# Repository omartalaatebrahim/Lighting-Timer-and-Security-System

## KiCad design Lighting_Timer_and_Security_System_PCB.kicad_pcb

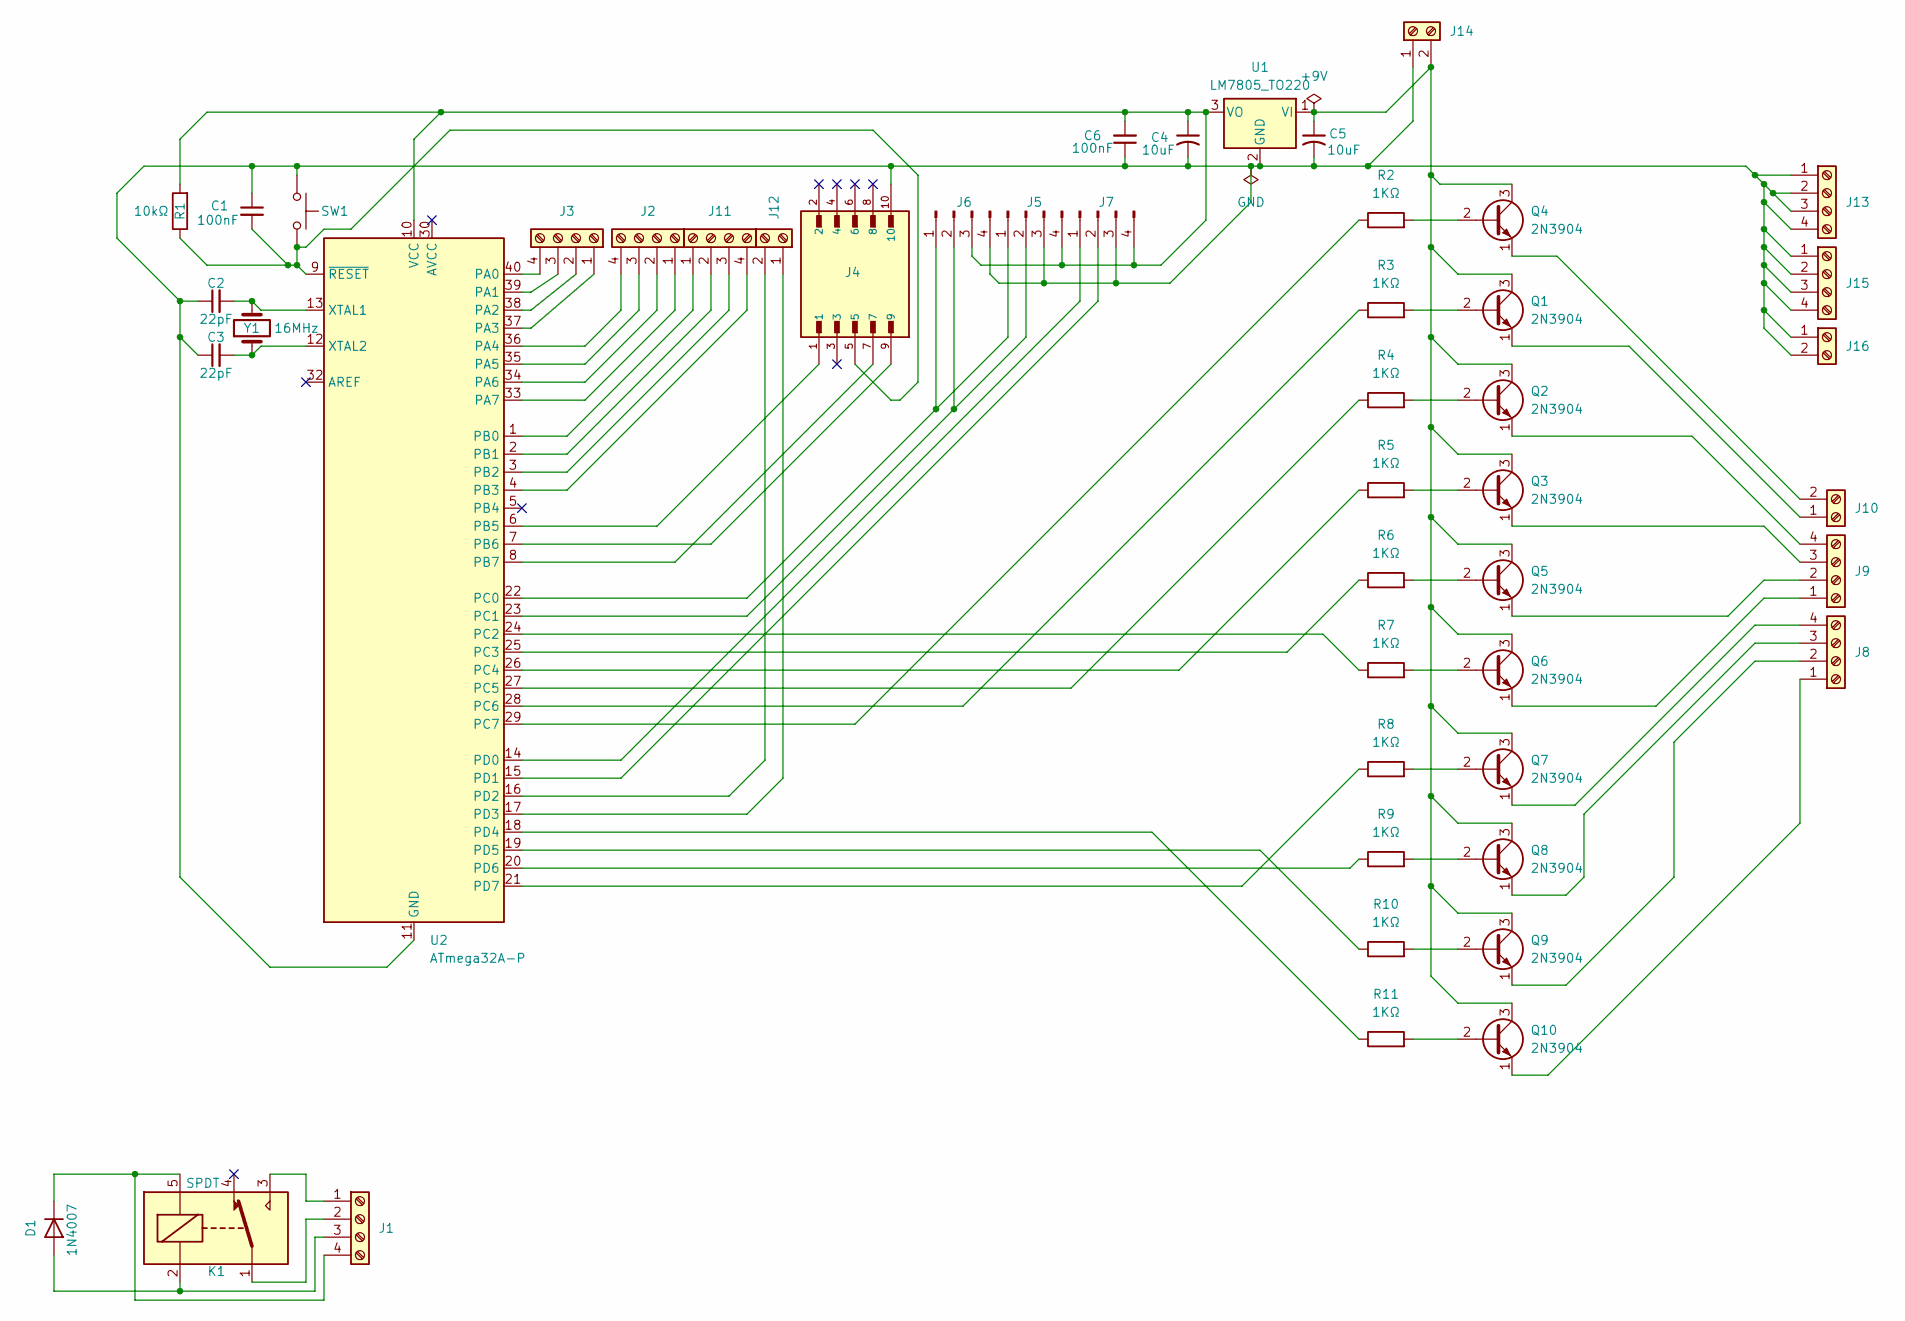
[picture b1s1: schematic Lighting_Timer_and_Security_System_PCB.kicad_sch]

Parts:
C1, C6: 100nF; C_Disc_D5.0mm_W2.5mm_P5.00mm
C2, C3: 22pF; C_Disc_D5.0mm_W2.5mm_P5.00mm
C4, C5: 10uF; CP_Radial_D5.0mm_P2.50mm
D1: 1N4007; D_DO-41_SOD81_P10.16mm_Horizontal
J1: T; TerminalBlock_MaiXu_MX126-5.0-04P_1x04_P5.00mm
J2, J3, J11: A0_A3_Terminals; TerminalBlock_MaiXu_MX126-5.0-04P_1x04_P5.00mm
J4: SBH11-PBPC-D05-ST-BK; SULLINS_SBH11-PBPC-D05-ST-BK; PARTREV J
J5: I2C; PinHeader_1x04_P2.54mm_Vertical
J6: DS3231_Timer; PinHeader_1x04_P2.54mm_Vertical
J7: UART; PinHeader_1x04_P2.54mm_Vertical
J8, J9: SIG_Terminals; TerminalBlock_MaiXu_MX126-5.0-04P_1x04_P5.00mm
J10: SIG_Terminals; TerminalBlock_MaiXu_MX126-5.0-02P_1x02_P5.00mm
J12, J14: Screw_Terminal_01x02; TerminalBlock_MaiXu_MX126-5.0-02P_1x02_P5.00mm
J13, J15: GND_Terminals; TerminalBlock_MaiXu_MX126-5.0-04P_1x04_P5.00mm
J16: GND_Terminals; TerminalBlock_MaiXu_MX126-5.0-02P_1x02_P5.00mm
K1: SPDT; Relay_SPDT_SANYOU_SRD_Series_Form_C
Q1, Q2, Q3, Q4, Q5, Q6, Q7, Q8, Q9, Q10: 2N3904; TO-92_Inline
R1: 10kΩ; R_Axial_DIN0207_L6.3mm_D2.5mm_P7.62mm_Horizontal
R2, R3, R4, R5, R6, R7, R8, R9, R10, R11: 1KΩ; R_Axial_DIN0207_L6.3mm_D2.5mm_P7.62mm_Horizontal
SW1: SW_Push; SW_PUSH_6mm
U1: LM7805_TO220; TO-220-3_Vertical
U2: ATmega32A-P; DIP-40_W15.24mm
Y1: 16MHz; Crystal_HC49-U_Vertical

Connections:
unnamed: D1.2 (A), J1.3, K1.2
unnamed: D1.1 (K), J1.4, K1.5
unnamed: J1.1, K1.3
unnamed: J1.2, K1.1
unnamed: J2.1, U2.33 (PA7)
unnamed: J2.2, U2.34 (PA6)
unnamed: J2.3, U2.35 (PA5)
unnamed: J2.4, U2.36 (PA4)
unnamed: J3.1, U2.37 (PA3)
unnamed: J3.2, U2.38 (PA2)
unnamed: J3.3, U2.39 (PA1)
unnamed: J3.4, U2.40 (PA0)
unnamed: J5.1, J6.1, U2.22 (PC0)
unnamed: J5.2, J6.2, U2.23 (PC1)
unnamed: C4.1, C6.2, J5.4, J6.3, J7.4, R1.2, U1.3 (VO), U2.10 (VCC)
unnamed: J7.1, U2.14 (PD0)
unnamed: J7.2, U2.15 (PD1)
unnamed: J8.1, Q10.1 (E)
unnamed: J8.2, Q9.1 (E)
unnamed: J8.3, Q8.1 (E)
unnamed: J8.4, Q7.1 (E)
unnamed: J9.1, Q6.1 (E)
unnamed: J9.2, Q5.1 (E)
unnamed: J9.3, Q3.1 (E)
unnamed: J9.4, Q2.1 (E)
unnamed: J10.1, Q1.1 (E)
unnamed: J10.2, Q4.1 (E)
unnamed: J11.1, U2.1 (PB0)
unnamed: J11.2, U2.2 (PB1)
unnamed: J11.3, U2.3 (PB2)
unnamed: J11.4, U2.4 (PB3)
unnamed: J12.1, U2.17 (PD3)
unnamed: J12.2, U2.16 (PD2)
unnamed: C1.1, C2.1, C3.1, C4.2, C5.2, C6.1, J4.10, J5.3, J6.4, J7.3, J13.1, J13.2, J13.3, J13.4, J14.1, J15.1, J15.2, J15.3, J15.4, J16.1, J16.2, SW1.1, U1.2 (GND), U2.11 (GND), U2.31 (GND)
unnamed: C5.1, J14.2, Q1.3 (C), Q2.3 (C), Q3.3 (C), Q4.3 (C), Q5.3 (C), Q6.3 (C), Q7.3 (C), Q8.3 (C), Q9.3 (C), Q10.3 (C), U1.1 (VI)
unnamed: Q1.2 (B), R3.2
unnamed: Q2.2 (B), R4.2
unnamed: Q3.2 (B), R5.2
unnamed: Q4.2 (B), R2.2
unnamed: Q5.2 (B), R6.2
unnamed: Q6.2 (B), R7.2
unnamed: Q7.2 (B), R8.2
unnamed: Q8.2 (B), R9.2
unnamed: Q9.2 (B), R10.2
unnamed: Q10.2 (B), R11.2
unnamed: J4.1, U2.6 (PB5)
unnamed: J4.9, U2.7 (PB6)
unnamed: J4.7, U2.8 (PB7)
unnamed: R7.1, U2.24 (PC2)
unnamed: R6.1, U2.25 (PC3)
unnamed: R5.1, U2.26 (PC4)
unnamed: R4.1, U2.27 (PC5)
unnamed: R3.1, U2.28 (PC6)
unnamed: R2.1, U2.29 (PC7)
unnamed: R11.1, U2.18 (PD4)
unnamed: R10.1, U2.19 (PD5)
unnamed: R9.1, U2.20 (PD6)
unnamed: R8.1, U2.21 (PD7)
unnamed: C2.2, U2.13 (XTAL1), Y1.2
unnamed: C3.2, U2.12 (XTAL2), Y1.1
unnamed: C1.2, J4.5, R1.1, SW1.2, U2.9 (~RESET)

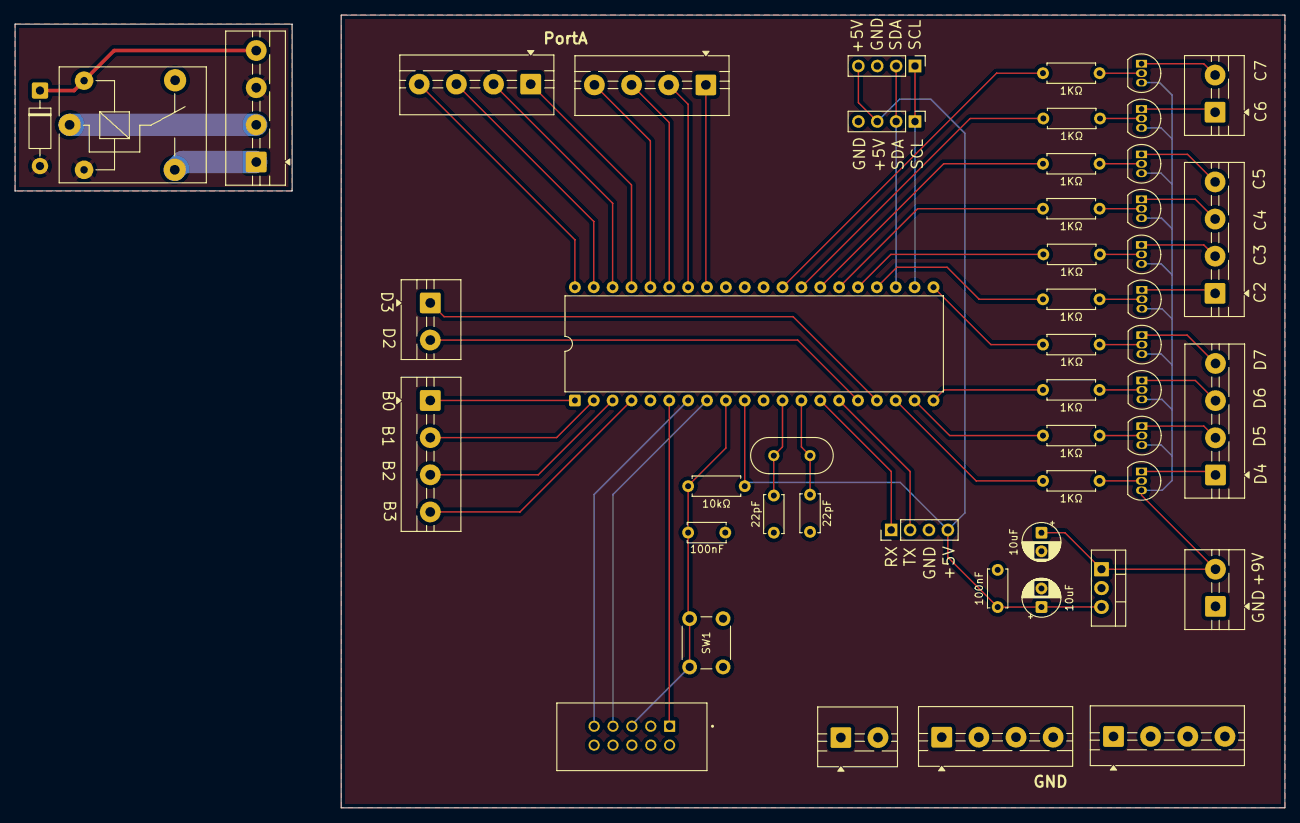
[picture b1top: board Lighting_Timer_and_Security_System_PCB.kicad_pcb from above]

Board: 2 copper layers, 127.0 x 106.7 mm, 49 parts (0 on the bottom side), 61 nets.
